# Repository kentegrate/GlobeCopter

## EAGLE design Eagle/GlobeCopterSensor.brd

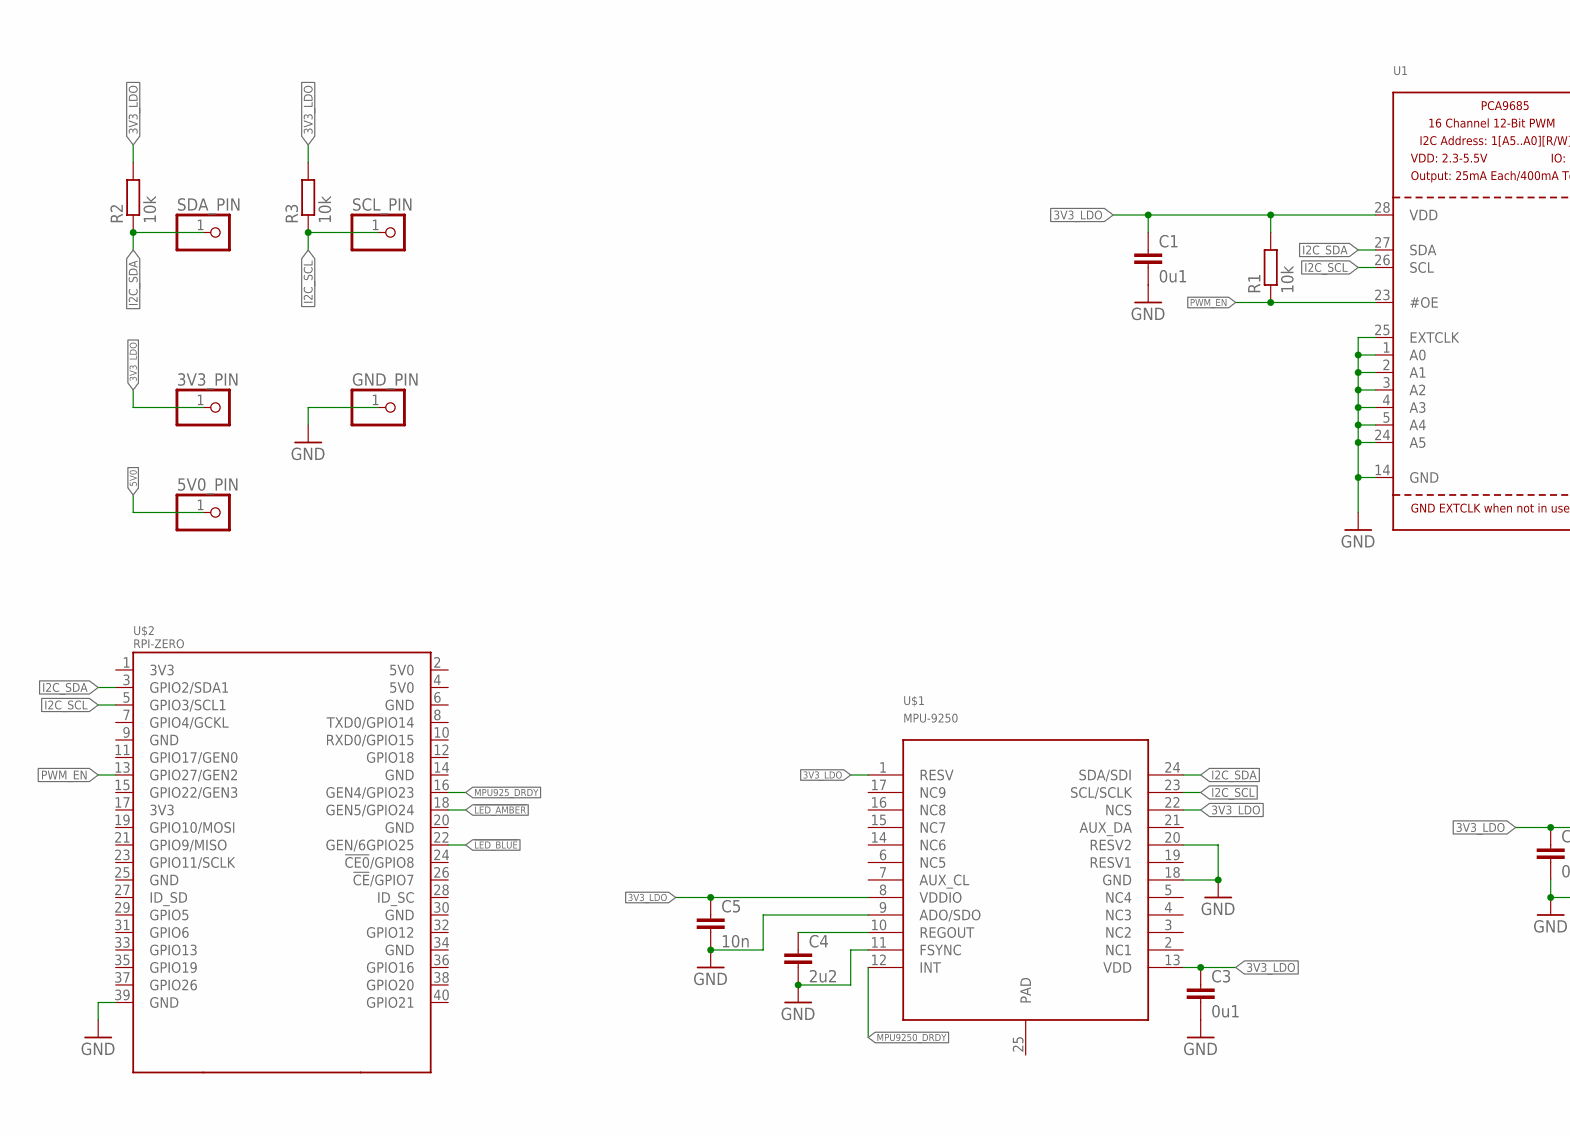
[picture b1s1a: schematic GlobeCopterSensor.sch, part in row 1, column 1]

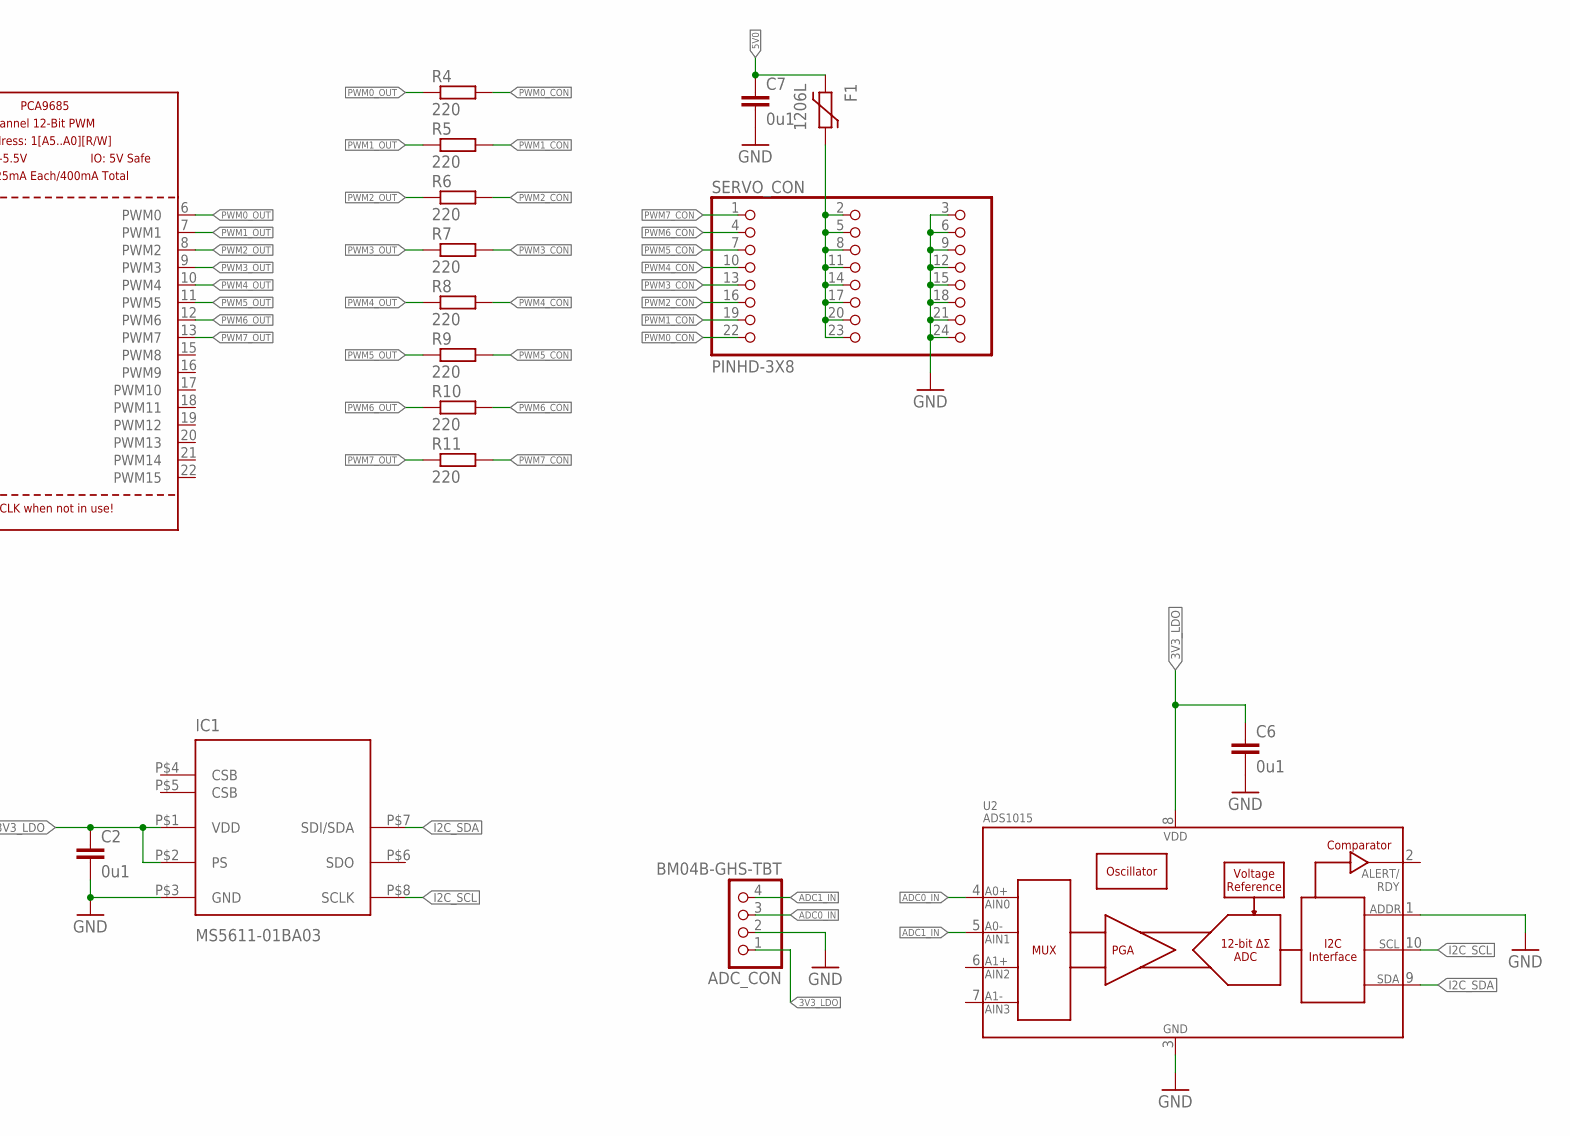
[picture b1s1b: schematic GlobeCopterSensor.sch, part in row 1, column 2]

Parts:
3V3_PIN, 5V0_PIN: PINHD-1X1; 1X01
ADC_CON: BM04B-GHS-TBT
C1, C2, C3, C6, C7: 0u1; C0603
C4: 2u2; C0603
C5: 10n; C0603
F1: 1206L
GND_PIN: PINHD-1X1; 1X01
IC1: MS5611-01BA03
R1, R2, R3: 10k; R0603
R4, R5, R6, R7, R8, R9, R10, R11: 220; R0603
SCL_PIN: PINHD-1X1; 1X01
SDA_PIN: PINHD-1X1; 1X01
SERVO_CON: PINHD-3X8; 3X8
U1: PCA9685; TSSOP28
U2: ADS1015; MSOP10
U$1: MPU-9250; LEAD-QFN24
U$2: RPI-ZERO; RASPBERRYPI_BASTELSTUBE_V13_RASPI_BOARD_B+_FULL

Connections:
3V3_LDO: 3V3_PIN.1, ADC_CON.1, C1.1, C2.1, C3.1, C5.1, C6.1, IC1.P$1 (VDD), IC1.P$2 (PS), R1.2, R2.2, R3.2, U1.28 (VDD), U2.8 (VDD), U$1.1 (RESV), U$1.8 (VDDIO), U$1.13 (VDD), U$1.22 (NCS)
5V0: 5V0_PIN.1, C7.1, F1.P$1 (1)
!LED_AMBER!: U$2.18 (GEN5/GPIO24)
!LED_BLUE!: U$2.22 (GEN/6GPIO25)
ADC0_IN: ADC_CON.3, U2.4 (AIN0)
ADC1_IN: ADC_CON.4, U2.5 (AIN1)
GND: ADC_CON.2, C1.2, C2.2, C3.2, C4.2, C5.2, C6.2, C7.2, GND_PIN.1, IC1.P$3 (GND), SERVO_CON.3, SERVO_CON.6, SERVO_CON.9, SERVO_CON.12, SERVO_CON.15, SERVO_CON.18, SERVO_CON.21, SERVO_CON.24, U1.1 (A0), U1.2 (A1), U1.3 (A2), U1.4 (A3), U1.5 (A4), U1.14 (GND), U1.24 (A5), U1.25 (EXTCLK), U2.1 (ADDR), U2.3 (VSS), U$1.9 (ADO/SDO), U$1.11 (FSYNC), U$1.18 (GND), U$1.20 (RESV2), U$2.39 (GND)
I2C_SCL: IC1.P$8 (SCLK), R3.1, SCL_PIN.1, U1.26 (SCL), U2.10 (SCL), U$1.23 (SCL/SCLK), U$2.5 (GPIO3/SCL1)
I2C_SDA: IC1.P$7 (SDI/SDA), R2.1, SDA_PIN.1, U1.27 (SDA), U2.9 (SDA), U$1.24 (SDA/SDI), U$2.3 (GPIO2/SDA1)
MPU925_DRDY: U$2.16 (GEN4/GPIO23)
MPU9250_DRDY: U$1.12 (INT)
unnamed: C4.1, U$1.10 (REGOUT)
unnamed: F1.P$2 (2), SERVO_CON.2, SERVO_CON.5, SERVO_CON.8, SERVO_CON.11, SERVO_CON.14, SERVO_CON.17, SERVO_CON.20, SERVO_CON.23
PWM0_CON: R4.2, SERVO_CON.22
PWM0_OUT: R4.1, U1.6 (PWM0)
PWM1_CON: R5.2, SERVO_CON.19
PWM1_OUT: R5.1, U1.7 (PWM1)
PWM2_CON: R6.2, SERVO_CON.16
PWM2_OUT: R6.1, U1.8 (PWM2)
PWM3_CON: R7.2, SERVO_CON.13
PWM3_OUT: R7.1, U1.9 (PWM3)
PWM4_CON: R8.2, SERVO_CON.10
PWM4_OUT: R8.1, U1.10 (PWM4)
PWM5_CON: R9.2, SERVO_CON.7
PWM5_OUT: R9.1, U1.11 (PWM5)
PWM6_CON: R10.2, SERVO_CON.4
PWM6_OUT: R10.1, U1.12 (PWM6)
PWM7_CON: R11.2, SERVO_CON.1
PWM7_OUT: R11.1, U1.13 (PWM7)
PWM_EN: R1.1, U1.23 (#OE), U$2.13 (GPIO27/GEN2)

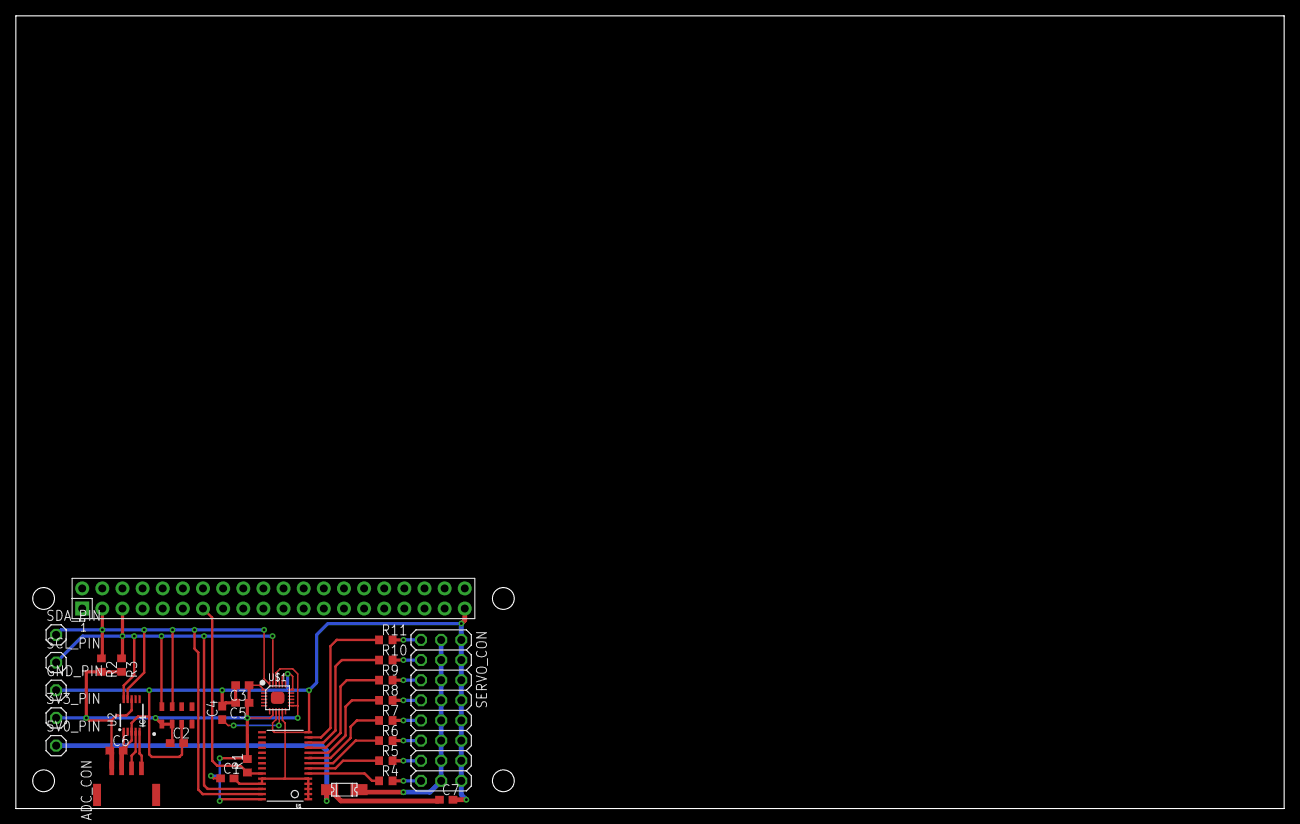
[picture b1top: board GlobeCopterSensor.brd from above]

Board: 2 copper layers, 160.0 x 100.0 mm, 31 parts (0 on the bottom side), 26 nets.

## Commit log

2017-07-06 changed dir for eagle
2017-07-07 add .gitignore for Eagle project, add sch and brd file, add reference sch image files
2017-07-07 remove unused 3.3v tag, connect rpi gnd, add i2c pullup part
2017-08-02 センサー部の基本的な設計完了 電源部等細部要調整
2017-08-07 部品をすべて部品面に移動
2017-08-10 blink led
2017-08-10 first commit with stm32
2017-08-10 use Makefile generator
2017-08-10 more warnings
2017-08-12 fix Makefile

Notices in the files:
parts and their libraries:
SparkFun-AnalogIC: Licensing:Creative Commons ShareAlike 4.0 International - https://creativecommons.org/licenses/by-sa/4.0
